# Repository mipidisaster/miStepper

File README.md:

# miStepper
This library contains the files and support for creating and installed code for the miStepper Device.e with this device).

# Linked libraries:
## milibrary
This library makes use of an extra repository - ['milibrary'](https://github.com/mipidisaster/miLibrary), which is not included within this repository; due to it being a seperate one. So this will need to be included...
> It doesn't matter were this is stored, however it should be at a high enough level that any lower level scripts can make reference to it.

```
<project root>
  ├─ milibrary
  │      └─ <contents>
  └─ < other folders >
```

# Stack overview
> To be added

# Build Tree

develop
v1.1.0
* Changes made to the software to incorporate the motor HAL - Fan/Stepper, as well as changes to the USART interface (making it common with the 'miStepper_ROS' repository
* Issues [#4](https://github.com/mipidisaster/miStepper/issues/4) and [#5](https://github.com/mipidisaster/miStepper/issues/5) fixed
* Issue [#7](https://github.com/mipidisaster/miStepper/issues/7), partial progress has been made on working this - mainly that a single task now exists for the motors
* Submodules introduced for the 'miStepper_ROS' and 'miLibrary' repositories so as to manage which version(s) are appliable to this

v1.0.0
* Major update of build, changing the electronics (PCB):
  1. PCB/Electronics updated to include new Stepper IC - (issue [#1](https://github.com/mipidisaster/miStepper/issues/1))
  2. Hardware filtering on the voltage/current monitors
  3. Extra temperature sensors added - 2 onboard sensors, and 2 external sensors
  4. CAN interface improved, such that it not is compliant to the protocol/hardware
  5. 4 layer PCB, to aid thermal cooling

* Software code updated:
  1. Supports latest release of 'milibrary' - [v0.2.1](https://github.com/mipidisaster/miLibrary/tree/v0.2.1)
     * Closing issue [#3](https://github.com/mipidisaster/miStepper/issues/3)
  2. Update to support latest hardware additions
  > Note, external sensor support not provided currently, to be added in next release
  
  3. Re-structing of the code, such that it follows the ['Layered Software Architecure'](https://github.com/mipidisaster/miLibrary/wiki/Software-Architecture) as per milibrary wiki - (issue [#2](https://github.com/mipidisaster/miStepper/issues/2))

v0.1.0
* Initial release (to be used with [milibrary v0.1.0](https://github.com/mipidisaster/miLibrary/tree/v0.1.0))

# Wiki
The wiki for this can be found within the Github repository for this - > to be added

See https://github.com/mipidisaster/miLibrary/wiki for basic information on Eclipse setup/remote ROS downloading...

# Issues
If you find any issues with this library, please capture them within the Github repository issue area - https://github.com/mipidisaster/miStepper/issues.

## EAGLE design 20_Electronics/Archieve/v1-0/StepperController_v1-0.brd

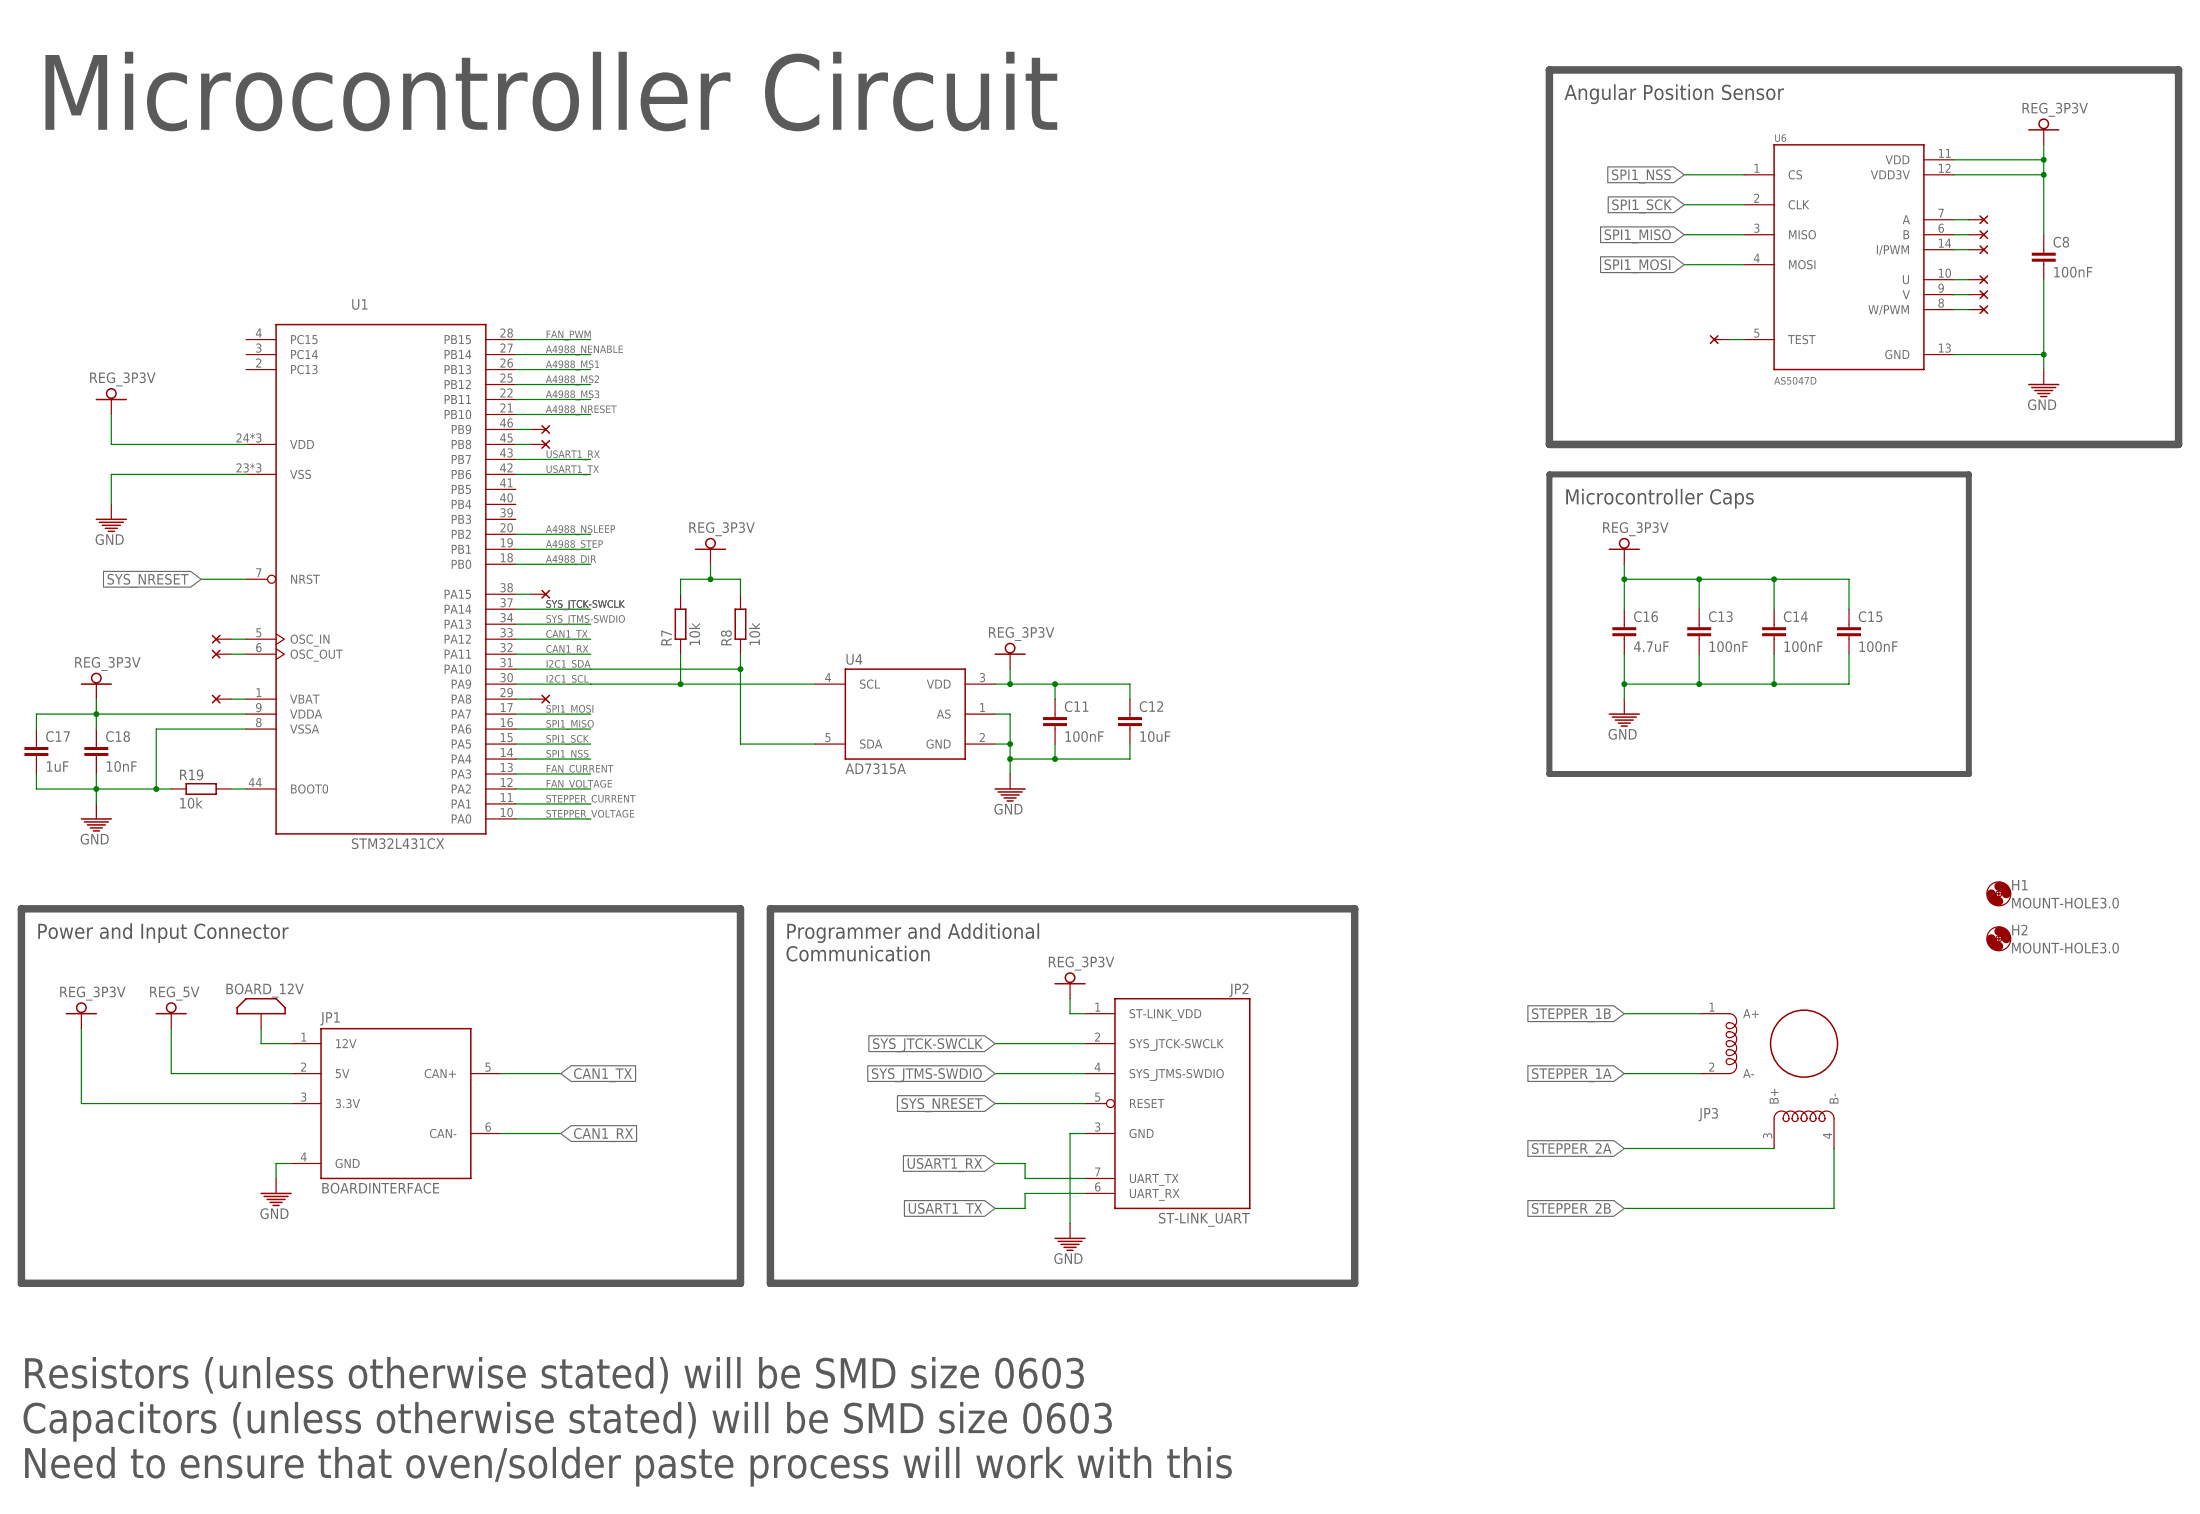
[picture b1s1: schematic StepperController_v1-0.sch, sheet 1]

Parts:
C8, C11, C13, C14, C15: 100nF; C0603
C12: 10uF; C0603
C16: 4.7uF; C0603
C17: 1uF; C0603
C18: 10nF; C0603
H1, H2: MOUNT-HOLE3.0; 3,0
JP1: BOARDINTERFACE; S6B-PH-SM4-TB
JP2: ST-LINK_UART; JP7
JP3: NEMA17; JP4
R7, R8, R19: 10k; R0603
U1: STM32L431CX; LQFP48
U4: AD7315A; SOT23-5L
U6: AS5047D; TSSOP14

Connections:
A4988_DIR: U1.18 (PB0); also elsewhere on the board
A4988_MS1: U1.26 (PB13); also elsewhere on the board
A4988_MS2: U1.25 (PB12); also elsewhere on the board
A4988_MS3: U1.22 (PB11); also elsewhere on the board
A4988_NENABLE: U1.27 (PB14); also elsewhere on the board
A4988_NRESET: U1.21 (PB10); also elsewhere on the board
A4988_NSLEEP: U1.20 (PB2); also elsewhere on the board
A4988_STEP: U1.19 (PB1); also elsewhere on the board
BOARD_12V: JP1.1 (12V); also elsewhere on the board
CAN1_RX: JP1.6 (CAN-), U1.32 (PA11)
CAN1_TX: JP1.5 (CAN+), U1.33 (PA12)
FAN_CURRENT: U1.13 (PA3); also elsewhere on the board
FAN_PWM: U1.28 (PB15); also elsewhere on the board
FAN_VOLTAGE: U1.12 (PA2); also elsewhere on the board
GND: C8.2, C11.2, C12.2, C13.2, C14.2, C15.2, C16.2, C17.2, C18.2, JP1.4 (GND), JP2.3 (GND), R19.1, U1.8 (VSSA), U1.23 (VSS), U1.35 (VSS), U1.47 (VSS), U4.1 (AS), U4.2 (GND), U6.13 (GND); also elsewhere on the board
I2C1_SCL: R7.1, U1.30 (PA9), U4.4 (SCL)
I2C1_SDA: R8.1, U1.31 (PA10), U4.5 (SDA)
unnamed: R19.2, U1.44 (BOOT0)
REG_3P3V: C8.1, C11.1, C12.1, C13.1, C14.1, C15.1, C16.1, C17.1, C18.1, JP1.3 (3.3V), JP2.1 (ST-LINK_VDD), R7.2, R8.2, U1.9 (VDDA), U1.24 (VDD), U1.36 (VDD), U1.48 (VDD), U4.3 (VDD), U6.11 (VDD), U6.12 (VDD3V); also elsewhere on the board
REG_5V: JP1.2 (5V); also elsewhere on the board
SPI1_MISO: U1.16 (PA6), U6.3 (MISO)
SPI1_MOSI: U1.17 (PA7), U6.4 (MOSI)
SPI1_NSS: U1.14 (PA4), U6.1 (CS)
SPI1_SCK: U1.15 (PA5), U6.2 (CLK)
STEPPER_1A: JP3.2 (A-); also elsewhere on the board
STEPPER_1B: JP3.1 (A+); also elsewhere on the board
STEPPER_2A: JP3.3 (B+); also elsewhere on the board
STEPPER_2B: JP3.4 (B-); also elsewhere on the board
STEPPER_CURRENT: U1.11 (PA1); also elsewhere on the board
STEPPER_VOLTAGE: U1.10 (PA0); also elsewhere on the board
SYS_JTCK-SWCLK: JP2.2 (SYS_JTCK-SWCLK), U1.37 (PA14)
SYS_JTMS-SWDIO: JP2.4 (SYS_JTMS-SWDIO), U1.34 (PA13)
SYS_NRESET: JP2.5 (RESET), U1.7 (NRST)
USART1_RX: JP2.7 (UART_TX), U1.43 (PB7)
USART1_TX: JP2.6 (UART_RX), U1.42 (PB6)

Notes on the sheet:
Microcontroller Caps
Angular Position Sensor
Resistors (unless otherwise stated) will be SMD size 0603 Capacitors (unless otherwise stated) will be SMD size 0603 Need to ensure that oven/solder paste process will work with this
Microcontroller Circuit
Power and Input Connector
Programmer and Additional Communication

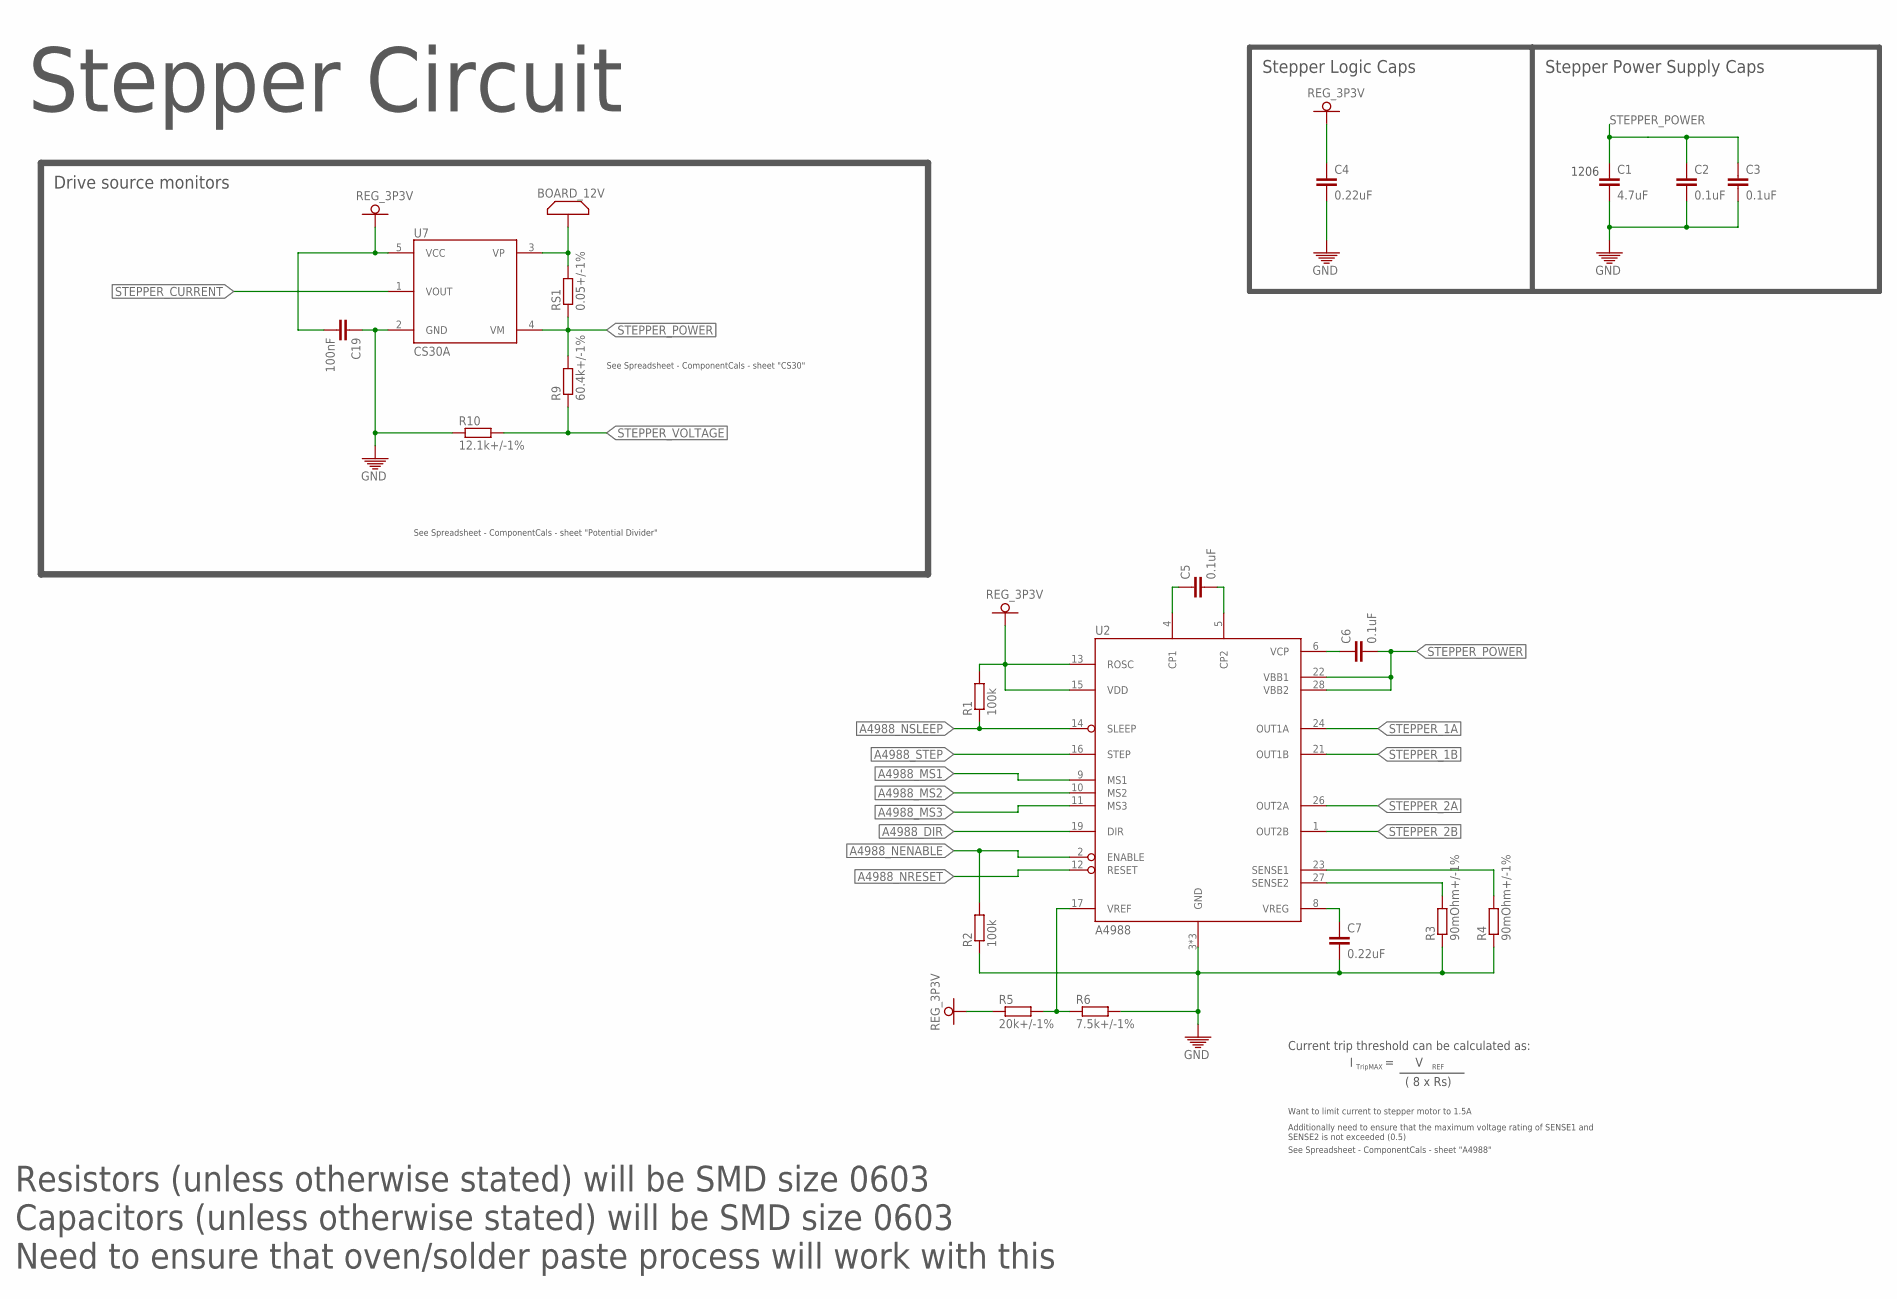
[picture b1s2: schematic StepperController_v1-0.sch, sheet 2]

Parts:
C1: 4.7uF; C1206
C2, C3, C5, C6: 0.1uF; C0603
C4, C7: 0.22uF; C0603
C19: 100nF; C0603
R1, R2: 100k; R0603
R3, R4: 90mOhm+/-1%; R0805
R5: 20k+/-1%; R0603
R6: 7.5k+/-1%; R0603
R9: 60.4k+/-1%; R0603
R10: 12.1k+/-1%; R0603
RS1: 0.05+/-1%; R0805
U2: A4988; QFN-28-5MM
U7: CS30A; SOT23-5L

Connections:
A4988_DIR: U2.19 (DIR); also elsewhere on the board
A4988_MS1: U2.9 (MS1); also elsewhere on the board
A4988_MS2: U2.10 (MS2); also elsewhere on the board
A4988_MS3: U2.11 (MS3); also elsewhere on the board
A4988_NENABLE: R2.2, U2.2 (ENABLE); also elsewhere on the board
A4988_NRESET: U2.12 (RESET); also elsewhere on the board
A4988_NSLEEP: R1.1, U2.14 (SLEEP); also elsewhere on the board
A4988_STEP: U2.16 (STEP); also elsewhere on the board
BOARD_12V: RS1.2, U7.3 (VP); also elsewhere on the board
GND: C1.2, C2.2, C3.2, C4.2, C7.2, C19.1, R2.1, R3.1, R4.1, R6.2, R10.1, U2.3 (GND), U2.18 (GND), U2.29 (GND), U7.2 (GND); also elsewhere on the board
unnamed: R3.2, U2.27 (SENSE2)
unnamed: C6.1, U2.6 (VCP)
unnamed: C5.1, U2.4 (CP1)
unnamed: C5.2, U2.5 (CP2)
unnamed: R4.2, U2.23 (SENSE1)
unnamed: C7.1, U2.8 (VREG)
unnamed: R5.2, R6.1, U2.17 (VREF)
REG_3P3V: C4.1, C19.2, R1.2, R5.1, U2.13 (ROSC), U2.15 (VDD), U7.5 (VCC); also elsewhere on the board
STEPPER_1A: U2.24 (OUT1A); also elsewhere on the board
STEPPER_1B: U2.21 (OUT1B); also elsewhere on the board
STEPPER_2A: U2.26 (OUT2A); also elsewhere on the board
STEPPER_2B: U2.1 (OUT2B); also elsewhere on the board
STEPPER_CURRENT: U7.1 (VOUT); also elsewhere on the board
STEPPER_POWER: C1.1, C2.1, C3.1, C6.2, R9.2, RS1.1, U2.22 (VBB1), U2.28 (VBB2), U7.4 (VM)
STEPPER_VOLTAGE: R9.1, R10.2; also elsewhere on the board

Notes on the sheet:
1206
Stepper Power Supply Caps
Stepper Logic Caps
Resistors (unless otherwise stated) will be SMD size 0603 Capacitors (unless otherwise stated) will be SMD size 0603 Need to ensure that oven/solder paste process will work with this
Current trip threshold can be calculated as:
I = V
TripMAX
REF
( 8 x Rs)
Want to limit current to stepper motor to 1.5A
Additionally need to ensure that the maximum voltage rating of SENSE1 and SENSE2 is not exceeded (0.5)
See Spreadsheet - ComponentCals - sheet "A4988"
Drive source monitors
See Spreadsheet - ComponentCals - sheet "CS30"
See Spreadsheet - ComponentCals - sheet "Potential Divider"
Stepper Circuit

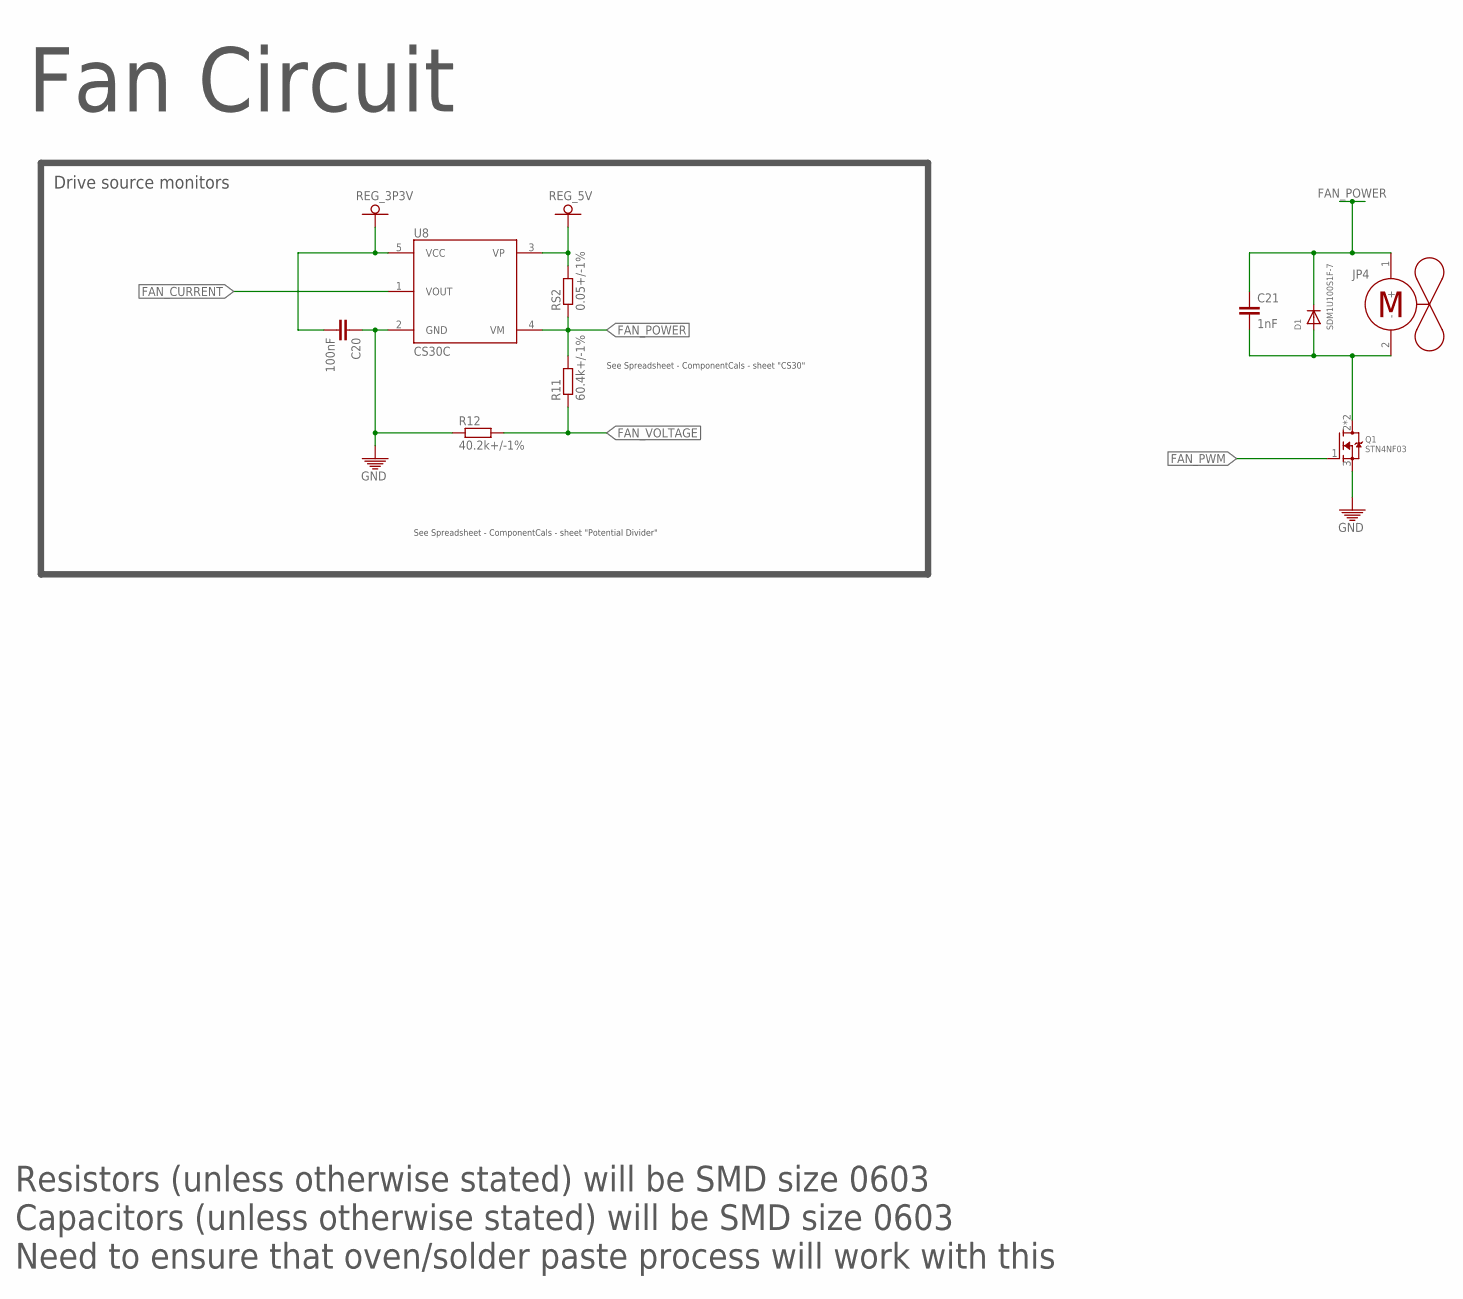
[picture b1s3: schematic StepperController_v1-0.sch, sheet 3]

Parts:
C20: 100nF; C0603
C21: 1nF; C0603
D1: SDM1U100S1F-7; SOD123F
JP4: MC33873; JP1Y
Q1: STN4NF03; SOT223
R11: 60.4k+/-1%; R0603
R12: 40.2k+/-1%; R0603
RS2: 0.05+/-1%; R0805
U8: CS30C; SOT23-5L

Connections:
FAN_CURRENT: U8.1 (VOUT); also elsewhere on the board
FAN_POWER: C21.1, D1.C, JP4.1 (+), R11.2, RS2.1, U8.4 (VM)
FAN_PWM: Q1.1 (G); also elsewhere on the board
FAN_VOLTAGE: R11.1, R12.2; also elsewhere on the board
GND: C20.1, Q1.3 (S), R12.1, U8.2 (GND); also elsewhere on the board
unnamed: C21.2, D1.A, JP4.2 (-), Q1.2 (D), Q1.4 (D)
REG_3P3V: C20.2, U8.5 (VCC); also elsewhere on the board
REG_5V: RS2.2, U8.3 (VP); also elsewhere on the board

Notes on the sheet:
See Spreadsheet - ComponentCals - sheet "CS30"
See Spreadsheet - ComponentCals - sheet "Potential Divider"
Resistors (unless otherwise stated) will be SMD size 0603 Capacitors (unless otherwise stated) will be SMD size 0603 Need to ensure that oven/solder paste process will work with this
Drive source monitors
Fan Circuit

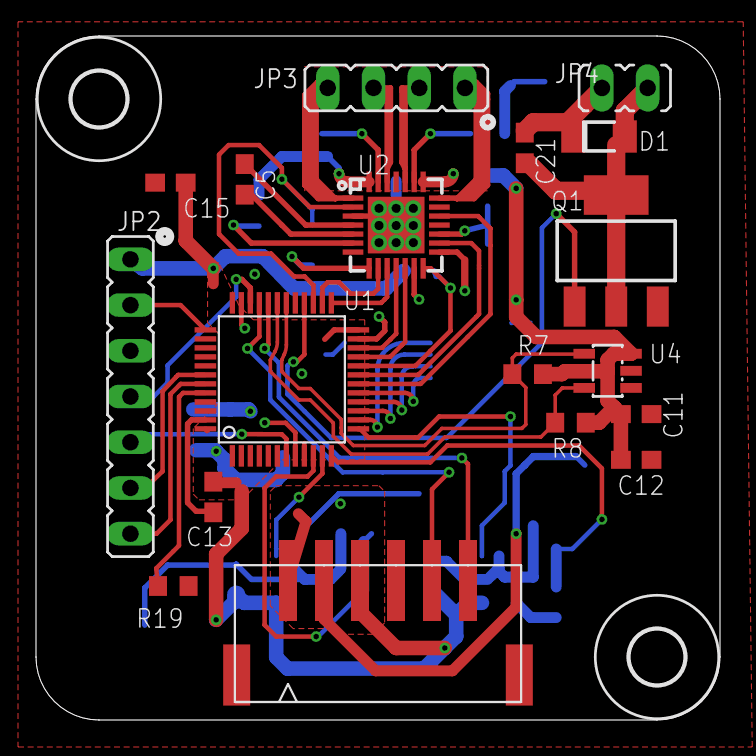
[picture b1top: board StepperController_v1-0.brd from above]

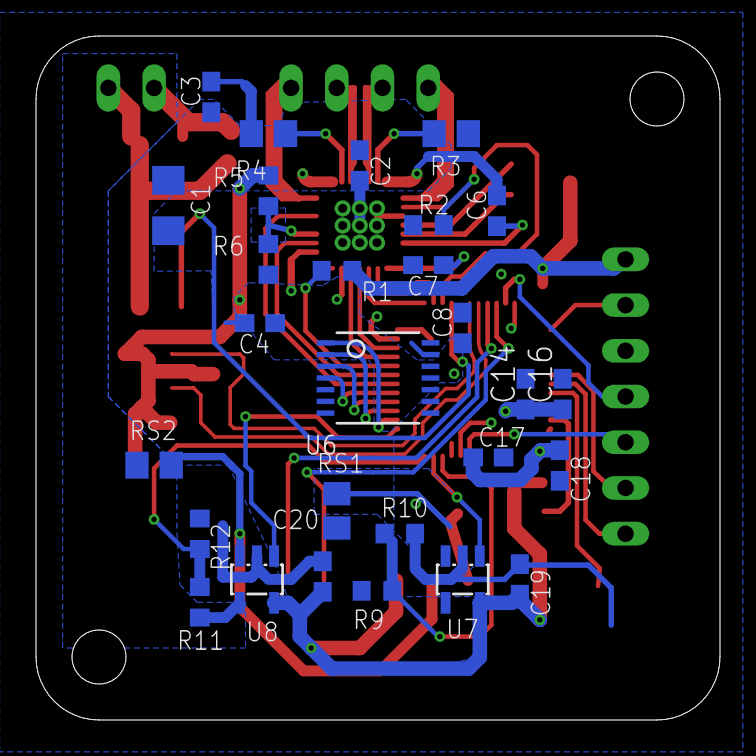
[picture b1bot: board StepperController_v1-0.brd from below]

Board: 2 copper layers, 38.0 x 38.0 mm, 48 parts (28 on the bottom side), 45 nets.

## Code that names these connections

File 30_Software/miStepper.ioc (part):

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Mcu.Name=STM32L431C(B-C)Tx
Mcu.Package=LQFP48
Mcu.UserName=STM32L431CBTx
PA0.GPIOParameters=GPIO_Label
PA0.GPIO_Label=ADC_STP_V
PA0.Signal=ADCx_IN5
PA1.GPIOParameters=GPIO_Label
PA1.GPIO_Label=ADC_STP_I
PA1.Signal=ADCx_IN6
PA10.GPIOParameters=GPIO_Speed
PA10.GPIO_Speed=GPIO_SPEED_FREQ_LOW
PA10.Mode=I2C
PA10.Signal=I2C1_SDA
PA11.GPIOParameters=GPIO_Label
PA11.GPIO_Label=STP_DIR
PA11.Signal=GPIO_Output
PA13\ (JTMS-SWDIO).Mode=Trace_Asynchronous_SW
PA13\ (JTMS-SWDIO).Signal=SYS_JTMS-SWDIO
PA14\ (JTCK-SWCLK).Mode=Trace_Asynchronous_SW
PA14\ (JTCK-SWCLK).Signal=SYS_JTCK-SWCLK
PA2.GPIOParameters=GPIO_Label
PA2.GPIO_Label=ADC_FAN_I
PA2.Signal=ADCx_IN7
PA3.GPIOParameters=GPIO_Label
PA3.GPIO_Label=ADC_FAN_V
PA3.Signal=ADCx_IN8
PA4.GPIOParameters=GPIO_Label
PA4.GPIO_Label=DAC_STP_IC_LIMIT-DRIVE
PA4.Signal=COMP_DAC11_group
PA5.GPIOParameters=GPIO_Speed
PA5.GPIO_Speed=GPIO_SPEED_FREQ_VERY_HIGH
PA5.Mode=Full_Duplex_Master
PA5.Signal=SPI1_SCK
PA6.GPIOParameters=GPIO_Speed
PA6.GPIO_Speed=GPIO_SPEED_FREQ_VERY_HIGH
PA6.Mode=Full_Duplex_Master
PA6.Signal=SPI1_MISO
PA7.GPIOParameters=GPIO_Speed
PA7.GPIO_Speed=GPIO_SPEED_FREQ_VERY_HIGH
PA7.Mode=Full_Duplex_Master
PA7.Signal=SPI1_MOSI
PA8.GPIOParameters=GPIO_Speed,PinState,GPIO_PuPd,GPIO_Label
PA8.GPIO_Label=CS_ANG_SENSOR
PA8.GPIO_PuPd=GPIO_NOPULL
PA8.GPIO_Speed=GPIO_SPEED_FREQ_HIGH
PA8.PinState=GPIO_PIN_SET
PA8.Signal=GPIO_Output
PA9.GPIOParameters=GPIO_Speed
PA9.GPIO_Speed=GPIO_SPEED_FREQ_LOW
PA9.Mode=I2C
PA9.Signal=I2C1_SCL
PB0.GPIOParameters=GPIO_Label
PB0.GPIO_Label=ADC_STP_IC_LIMIT
PB0.Signal=ADCx_IN15
PB1.GPIOParameters=GPIO_Label
PB1.GPIO_Label=STP_STEP-DRIVE
PB1.Mode=Output Compare3 CH3N
PB1.Signal=TIM1_CH3N
PB11.GPIOParameters=GPIO_Label
PB11.GPIO_Label=STP_MS3
PB11.Signal=GPIO_Output
PB12.GPIOParameters=GPIO_Label
PB12.GPIO_Label=STP_MS2
PB12.Signal=GPIO_Output
PB13.GPIOParameters=GPIO_Label
PB13.GPIO_Label=STP_MS1
PB13.Signal=GPIO_Output
PB14.GPIOParameters=PinState,GPIO_Label
PB14.GPIO_Label=STP_DECAY
PB14.PinState=GPIO_PIN_RESET
PB14.Signal=GPIO_Output
PB15.GPIOParameters=GPIO_Label
PB15.GPIO_Label=PWM_FAN-DRIVE
PB15.Signal=S_TIM15_CH2
PB2.GPIOParameters=GPIO_Label
PB2.GPIO_Label=STP_NSLEEP
PB2.Signal=GPIO_Output
PB3\ (JTDO-TRACESWO).Mode=Trace_Asynchronous_SW
PB3\ (JTDO-TRACESWO).Signal=SYS_JTDO-SWO
PB6.Mode=Asynchronous
PB6.Signal=USART1_TX
PB7.Mode=Asynchronous
PB7.Signal=USART1_RX
RCC.HSE_VALUE=8000000
RCC.SYSCLKFreq_VALUE=80000000
RCC.SYSCLKSource=RCC_SYSCLKSOURCE_PLLCLK
board=custom

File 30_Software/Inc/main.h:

/* USER CODE BEGIN Header */
/**
  ******************************************************************************
  * @file           : main.h
  * @brief          : Header for main.c file.
  *                   This file contains the common defines of the application.
  ******************************************************************************
  ** This notice applies to any and all portions of this file
  * that are not between comment pairs USER CODE BEGIN and
  * USER CODE END. Other portions of this file, whether 
  * inserted by the user or by software development tools
  * are owned by their respective copyright owners.
  *
  * COPYRIGHT(c) 2018 STMicroelectronics
  *
  * Redistribution and use in source and binary forms, with or without modification,
  * are permitted provided that the following conditions are met:
  *   1. Redistributions of source code must retain the above copyright notice,
  *      this list of conditions and the following disclaimer.
  *   2. Redistributions in binary form must reproduce the above copyright notice,
  *      this list of conditions and the following disclaimer in the documentation
  *      and/or other materials provided with the distribution.
  *   3. Neither the name of STMicroelectronics nor the names of its contributors
  *      may be used to endorse or promote products derived from this software
  *      without specific prior written permission.
  *
  * THIS SOFTWARE IS PROVIDED BY THE COPYRIGHT HOLDERS AND CONTRIBUTORS "AS IS"
  * AND ANY EXPRESS OR IMPLIED WARRANTIES, INCLUDING, BUT NOT LIMITED TO, THE
  * IMPLIED WARRANTIES OF MERCHANTABILITY AND FITNESS FOR A PARTICULAR PURPOSE ARE
  * DISCLAIMED. IN NO EVENT SHALL THE COPYRIGHT HOLDER OR CONTRIBUTORS BE LIABLE
  * FOR ANY DIRECT, INDIRECT, INCIDENTAL, SPECIAL, EXEMPLARY, OR CONSEQUENTIAL
  * DAMAGES (INCLUDING, BUT NOT LIMITED TO, PROCUREMENT OF SUBSTITUTE GOODS OR
  * SERVICES; LOSS OF USE, DATA, OR PROFITS; OR BUSINESS INTERRUPTION) HOWEVER
  * CAUSED AND ON ANY THEORY OF LIABILITY, WHETHER IN CONTRACT, STRICT LIABILITY,
  * OR TORT (INCLUDING NEGLIGENCE OR OTHERWISE) ARISING IN ANY WAY OUT OF THE USE
  * OF THIS SOFTWARE, EVEN IF ADVISED OF THE POSSIBILITY OF SUCH DAMAGE.
  *
  ******************************************************************************
  */
/* USER CODE END Header */

/* Define to prevent recursive inclusion -------------------------------------*/
#ifndef __MAIN_H
#define __MAIN_H

#ifdef __cplusplus
extern "C" {
#endif

/* Includes ------------------------------------------------------------------*/
#include "stm32l4xx_hal.h"

/* Private includes ----------------------------------------------------------*/
/* USER CODE BEGIN Includes */


/* USER CODE END Includes */

/* Exported types ------------------------------------------------------------*/
/* USER CODE BEGIN ET */

/* USER CODE END ET */

/* Exported constants --------------------------------------------------------*/
/* USER CODE BEGIN EC */

/* USER CODE END EC */

/* Exported macro ------------------------------------------------------------*/
/* USER CODE BEGIN EM */

/* USER CODE END EM */

void HAL_TIM_MspPostInit(TIM_HandleTypeDef *htim);

/* Exported functions prototypes ---------------------------------------------*/
void Error_Handler(void);

/* USER CODE BEGIN EFP */

/* USER CODE END EFP */

/* Private defines -----------------------------------------------------------*/
#define STEPPER_VOLTAGE_Pin GPIO_PIN_0
#define STEPPER_VOLTAGE_GPIO_Port GPIOA
#define STEPPER_CURRENT_Pin GPIO_PIN_1
#define STEPPER_CURRENT_GPIO_Port GPIOA
#define FAN_VOLTAGE_Pin GPIO_PIN_2
#define FAN_VOLTAGE_GPIO_Port GPIOA
#define FAN_CURRENT_Pin GPIO_PIN_3
#define FAN_CURRENT_GPIO_Port GPIOA
#define AS5048_Pin GPIO_PIN_4
#define AS5048_GPIO_Port GPIOA
#define A4988_DIR_Pin GPIO_PIN_0
#define A4988_DIR_GPIO_Port GPIOB
#define A4988_STEP_Pin GPIO_PIN_1
#define A4988_STEP_GPIO_Port GPIOB
#define A4988_NSLEEP_Pin GPIO_PIN_2
#define A4988_NSLEEP_GPIO_Port GPIOB
#define A4988_NRESET_Pin GPIO_PIN_10
#define A4988_NRESET_GPIO_Port GPIOB
#define A4988_MS3_Pin GPIO_PIN_11
#define A4988_MS3_GPIO_Port GPIOB
#define A4988_MS2_Pin GPIO_PIN_12
#define A4988_MS2_GPIO_Port GPIOB
#define A4988_MS1_Pin GPIO_PIN_13
#define A4988_MS1_GPIO_Port GPIOB
#define A4988_NENABLE_Pin GPIO_PIN_14
#define A4988_NENABLE_GPIO_Port GPIOB
#define PWM_FAN_Pin GPIO_PIN_15
#define PWM_FAN_GPIO_Port GPIOB
/* USER CODE BEGIN Private defines */

void TIM1_BRK_TIM15_IRQHandler(void);


/* USER CODE END Private defines */

#ifdef __cplusplus
}
#endif

#endif /* __MAIN_H */

/************************ (C) COPYRIGHT STMicroelectronics *****END OF FILE****/

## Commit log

2019-03-09 Initial version of 'miStepper' project, software is working correctly
2019-03-10 Electronics of version 1 of 'miStepper' hardware
2019-06-25 Embedded functions updated to provide a set of data via USART to a computer - Raspberry Pi, and read back a set of commands. This is going to be used to design the internal logic of the miStepper
2019-06-25 Previously gitted files updated again, to ensure that dates and versions get updated
2019-06-25 main source file updated to link together updated interfacing tasks
2019-09-04 Configuration file for miStepper updated to include some information on how the Stepper motor task iteration rate should be determined + spreadsheets added
2019-09-15 SPI/I2C tasks updated to align with updated design of SPIPeriph/I2CPeriph - such that it now uses just the arrays to link to the peripherals
2019-09-15 ADC task updated to include averaging of the 'ADC1_ConvPSeq'values captured per ADC run
2019-09-15 Correction to 'StpStatAct' generation to OR values, not clear
2019-09-15 Configuration header tidied up
2019-09-18 Update to the USART task due to update to the UARTPeriph class, to utilise the 'Form system'; next update will be using the DMA instead of interrupt based communication
2019-09-28 All tasks updated such that they no longer receive in a parameter with the linked hardware. It is instead called within the cpp as an extern variable Additionally, UART updated to utilise DMA.
    warning has been added to ADC, on the DMA as current call doesn't allow for re-allocating DMA pointers (as STM32CubeMX thinks the HAL is locked)
2019-11-15 All tasks updated such that they no longer receive in a parameter pointing to variables/builds/etc. Additionally USART task updated to include DMA and CRC
2019-11-15 main.cpp updated so no longer calls tasks with pointer
2021-10-09 Update to 'miStepper.ioc' and version of 'STM32CubeMX' (v6.2.1) generates different outputs. Embed folder and contents updated to align with new stucture, as per miLibrary wiki (Software Architecture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
2021-10-09 Archieve within '20_Electronics' deleted as not required due to github
2021-10-09 Removing unrequired files within 'Embed' due to code update
2021-10-09 Task utilisation spreadsheet added, and updated Timings spreadsheet commited
2021-10-09 Task Utilisation updated based upon the latest code
2021-10-16 Electronics schematics/GERBER files added for the mk2 version of the hardware. README file/Build Tree updated to state latest changes in next release
2021-10-16 Build Tree updated with the 'develop' line, and gitignore updated with comment on intent to setup this repository to have sub-modules from miStepper_ROS and milibrary - however need to understand thi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
2021-12-23 USART driver updated to align with latest working version of the miStepperUART class from milibrary
2021-12-23 USART driver task updated to align with name changes to 'miStepperUSART' members
2021-12-23 USART interface file updated to include the 'Control' function which facilitates the commands from user - via miStepper_ROS - into the miStepper Device. Note that this currently only supports FAN con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
2022-01-10 Fan demand parameter updated, due to some of the name already being captured as part of the namespace. i.e. name space is '_ifan', so there is no need to call the parameter 'fan_demand'
2022-01-10 Ref issue #4 and #5. Introduced HAL interface for the actual Stepper motor, making use of the updates to milibrary 'miStepperUSART'.
2022-01-10 Current limit updates to support change is test motor
2022-01-10 Ref issue #7. Update to the STM32CubeMX file to support change in the tasks for the motors to a single task. Task_Utilisation spreadsheet updates to get memory levels for latest build
2022-01-10 Pull request #14, raised to bring recent changes from 'develop' branch into the mainline - v1.1.0. Commit created to update diagrams, README file and include submodules for 'milibrary'/'miStepper_ROS'
2022-01-10 Updated build tree diagram to include flow of 'develop' branch
2022-01-17 submodule structure updated as can use Linux folder links instead of original plan
2022-01-17 Fixes #14
2022-01-17 Closes #14
2022-03-06 Minor changes made to the layout of the SPI task (similar to what has been done to the I2C tasks), such that all space related parameters are captured within the 'parameter.hpp' header. As well as mo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
2022-03-06 Ref issue #15. Introduced extra device BME280, which has been tested and all appears to work correctly. Currenly configured to capture temperature, pressure and humidity - probably don't need the las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
2022-03-06 Ref issue #15. ihal file updated to include the new parameters captured from the BME280 device(s)
2022-03-06 Utilisation updated to show how the size of I2C has been consumed with the introduction of the BME280 controller

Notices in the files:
parts and their libraries:
Licensing: CC v3.0 Share-Alike You are welcome to use this library for commercial purposes.
